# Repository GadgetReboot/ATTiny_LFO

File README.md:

# ATTiny_LFO
<br><br><BR><BR>
Dual low frequency oscillators using ATTiny and MCP4725 DACs

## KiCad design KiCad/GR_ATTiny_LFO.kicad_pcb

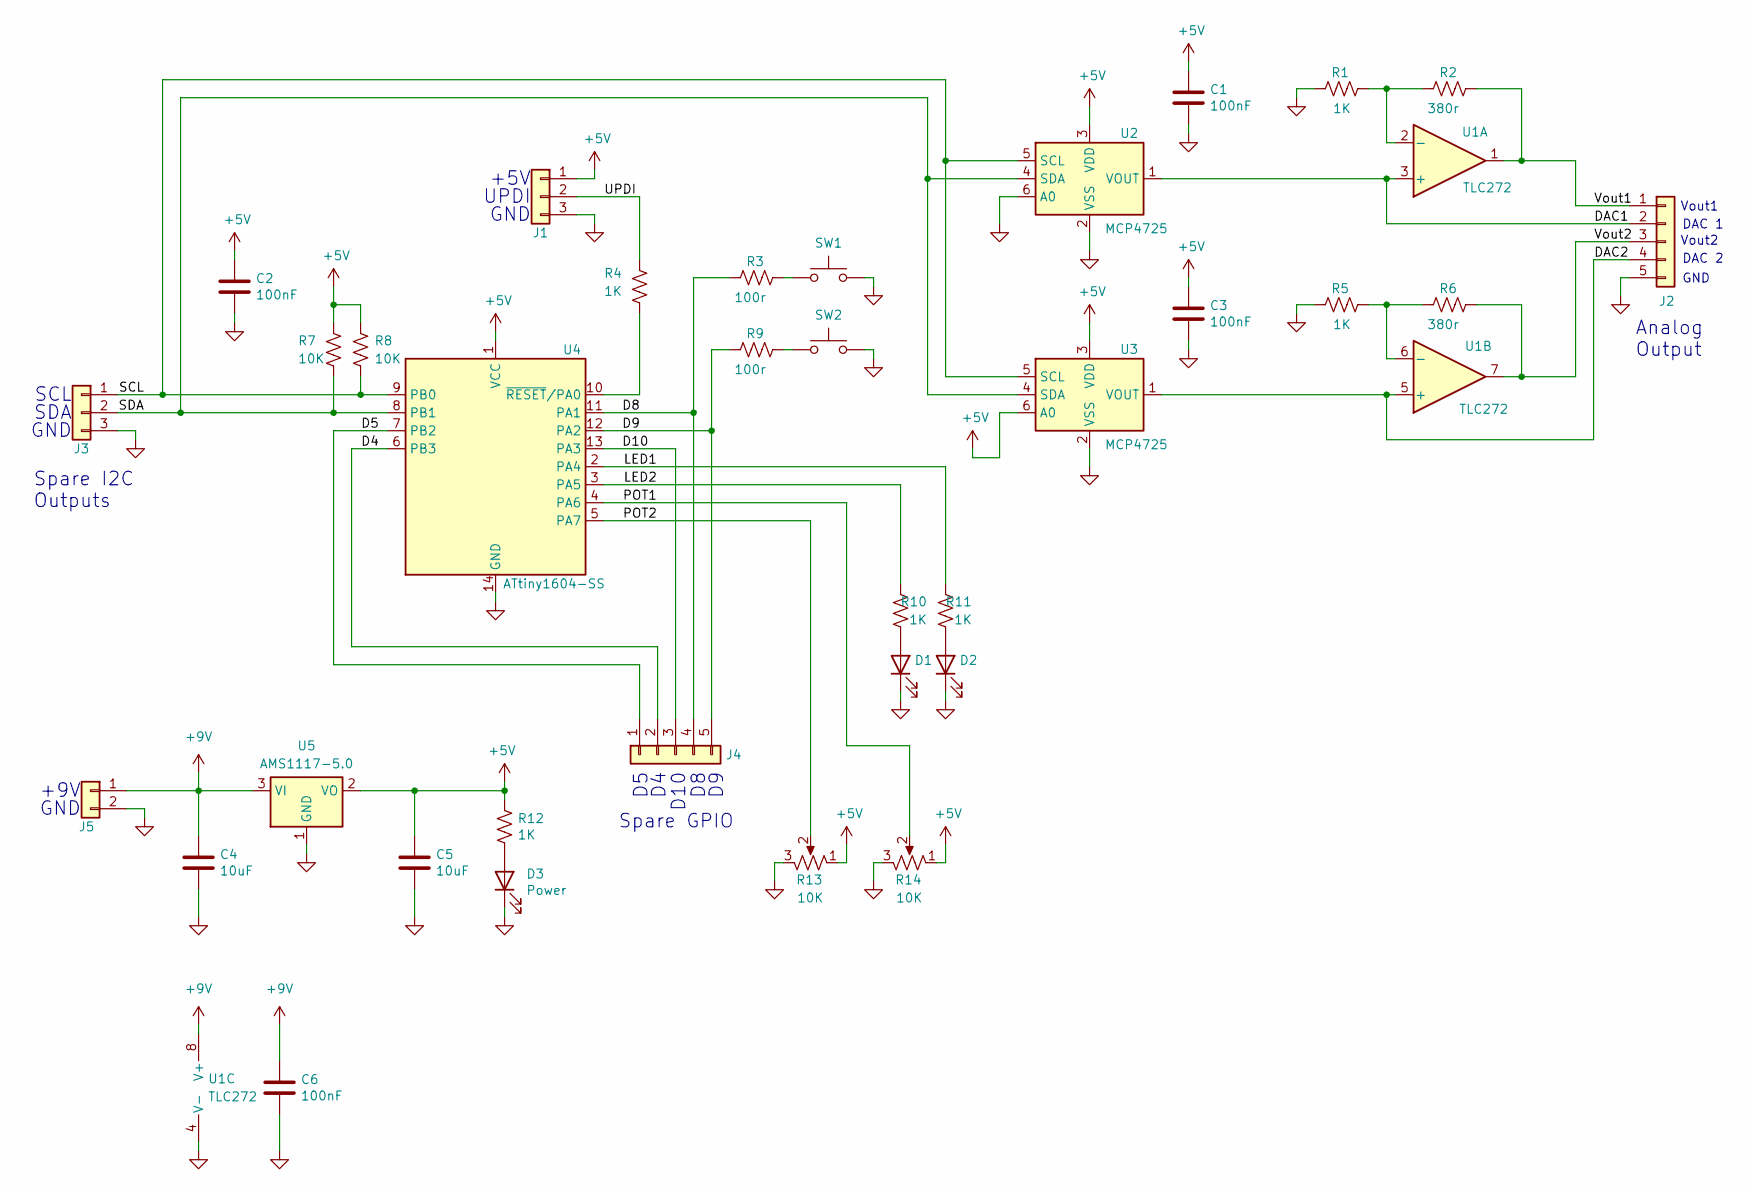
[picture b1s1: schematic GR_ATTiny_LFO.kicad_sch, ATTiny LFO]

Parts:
C1, C3, C6: 100nF; C_0805_2012Metric_Pad1.15x1.40mm_HandSolder
C2: 100nF; C_0805_2012Metric_Pad1.18x1.45mm_HandSolder
C4, C5: 10uF; C_0805_2012Metric_Pad1.15x1.40mm_HandSolder
D1, D2: LED; LED_0805_2012Metric_Pad1.15x1.40mm_HandSolder
D3: Power; LED_0805_2012Metric_Pad1.15x1.40mm_HandSolder
J1, J3: Conn_01x03; PinHeader_1x03_P2.54mm_Vertical
J2, J4: Conn_01x05; PinHeader_1x05_P2.54mm_Vertical
J5: 1x2; PinHeader_1x02_P2.54mm_Vertical
R1, R4, R5, R10, R11, R12: 1K; R_0805_2012Metric_Pad1.15x1.40mm_HandSolder
R2, R6: 380r; R_0805_2012Metric_Pad1.15x1.40mm_HandSolder
R3, R9: 100r; R_0805_2012Metric_Pad1.15x1.40mm_HandSolder
R7, R8: 10K; R_0805_2012Metric_Pad1.15x1.40mm_HandSolder
R13, R14: 10K; Potentiometer_Bourns_PTV09A-1
SW1, SW2: SW_Push; SW_SPST_60x35
U1: TLC272; SOIC-8_3.9x4.9mm_P1.27mm
U2, U3: MCP4725; SOT-23-6
U4: ATtiny1604-SS; SOIC-14_3.9x8.7mm_P1.27mm
U5: AMS1117-5.0; SOT-223-3_TabPin2

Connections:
+5V: C1.1, C2.1, C3.1, C5.1, J1.1, R7.1, R8.1, R12.1, R13.1, R14.1, U2.3 (VDD), U3.3 (VDD), U3.6 (A0), U4.1 (VCC), U5.2 (VO)
+9V: C4.1, C6.1, J5.1, U1.8 (V+), U5.3 (VI)
/D4: J4.2, U4.6 (PB3)
/D5: J4.1, U4.7 (PB2)
/D8: J4.4, R3.1, U4.11 (PA1)
/D9: J4.5, R9.1, U4.12 (PA2)
/D10: J4.3, U4.13 (PA3)
/DAC1: J2.2, U1.3 (+), U2.1 (VOUT)
/DAC2: J2.4, U1.5 (+), U3.1 (VOUT)
/LED1: R11.2, U4.2 (PA4)
/LED2: R10.2, U4.3 (PA5)
/POT1: R14.2, U4.4 (PA6)
/POT2: R13.2, U4.5 (PA7)
/SCL: J3.1, R8.2, U2.5 (SCL), U3.5 (SCL), U4.9 (PB0)
/SDA: J3.2, R7.2, U2.4 (SDA), U3.4 (SDA), U4.8 (PB1)
/UPDI: J1.2, R4.1
/Vout1: J2.1, R2.2, U1.1
/Vout2: J2.3, R6.2, U1.7
GND: C1.2, C2.2, C3.2, C4.2, C5.2, C6.2, D1.1 (K), D2.1 (K), D3.1 (K), J1.3, J2.5, J3.3, J5.2, R1.1, R5.1, R13.3, R14.3, SW1.2, SW2.2, U1.4 (V-), U2.2 (VSS), U2.6 (A0), U3.2 (VSS), U4.14 (GND), U5.1 (GND)
unnamed: D1.2 (A), R10.1
unnamed: D2.2 (A), R11.1
unnamed: D3.2 (A), R12.2
unnamed: R3.2, SW1.1
unnamed: R9.2, SW2.1
unnamed: R1.2, R2.1, U1.2 (-)
unnamed: R5.2, R6.1, U1.6 (-)
unnamed: R4.2, U4.10 (~RESET/PA0)

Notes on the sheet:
UPDI
GND
Spare GPIO
+5V
SDA
+9V
Spare I2C Outputs
DAC 2
D10
Vout2
Vout1
DAC 1
SCL
Analog Output

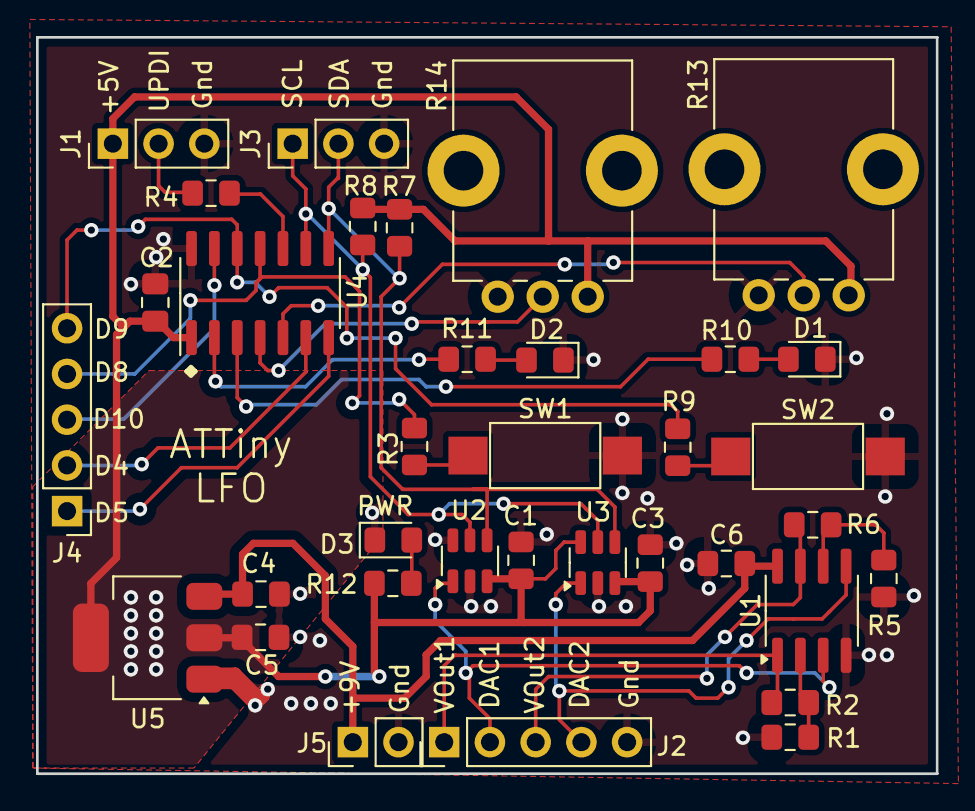
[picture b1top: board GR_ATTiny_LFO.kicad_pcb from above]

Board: 2 copper layers, 50.0 x 40.9 mm, 35 parts (0 on the bottom side), 27 nets.

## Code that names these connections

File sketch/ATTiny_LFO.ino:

/*
     Dual MCP4725 12-bit DACs
     Generating low frequency waveforms
     Uses ATTiny 1604
     Uses Adafruit MCP4725 library
     Uses Bounce2 library https://github.com/thomasfredericks/Bounce2

youtube.com/@GadgetReboot
*/

#include <Wire.h>
#include <Bounce2.h>
#include <Adafruit_MCP4725.h>

// create objects to access the LFO dacs
Adafruit_MCP4725 LFO1;
Adafruit_MCP4725 LFO2;

// button debouncers
Bounce button1 = Bounce();
Bounce button2 = Bounce();

// button and led pins assigned to Arduino digital pin numbers by mapping chip port pins from
// https://github.com/SpenceKonde/megaTinyCore/blob/master/megaavr/extras/ATtiny_x04.md
const byte btn1 = 8;
const byte btn2 = 9;
const byte led1 = 0;
const byte led2 = 1;
const byte pot1 = 2;
const byte pot2 = 3;

// sine waveform data table
const PROGMEM uint16_t sine_data[256] = {
  2048, 2098, 2148, 2198, 2248, 2298, 2348, 2398,
  2447, 2496, 2545, 2594, 2642, 2690, 2737, 2784,
  2831, 2877, 2923, 2968, 3013, 3057, 3100, 3143,
  3185, 3226, 3267, 3307, 3346, 3385, 3423, 3459,
  3495, 3530, 3565, 3598, 3630, 3662, 3692, 3722,
  3750, 3777, 3804, 3829, 3853, 3876, 3898, 3919,
  3939, 3958, 3975, 3992, 4007, 4021, 4034, 4045,
  4056, 4065, 4073, 4080, 4085, 4089, 4093, 4094,
  4095, 4094, 4093, 4089, 4085, 4080, 4073, 4065,
  4056, 4045, 4034, 4021, 4007, 3992, 3975, 3958,
  3939, 3919, 3898, 3876, 3853, 3829, 3804, 3777,
  3750, 3722, 3692, 3662, 3630, 3598, 3565, 3530,
  3495, 3459, 3423, 3385, 3346, 3307, 3267, 3226,
  3185, 3143, 3100, 3057, 3013, 2968, 2923, 2877,
  2831, 2784, 2737, 2690, 2642, 2594, 2545, 2496,
  2447, 2398, 2348, 2298, 2248, 2198, 2148, 2098,
  2048, 1997, 1947, 1897, 1847, 1797, 1747, 1697,
  1648, 1599, 1550, 1501, 1453, 1405, 1358, 1311,
  1264, 1218, 1172, 1127, 1082, 1038, 995, 952,
  910, 869, 828, 788, 749, 710, 672, 636,
  600, 565, 530, 497, 465, 433, 403, 373,
  345, 318, 291, 266, 242, 219, 197, 176,
  156, 137, 120, 103, 88, 74, 61, 50,
  39, 30, 22, 15, 10, 6, 2, 1,
  0, 1, 2, 6, 10, 15, 22, 30,
  39, 50, 61, 74, 88, 103, 120, 137,
  156, 176, 197, 219, 242, 266, 291, 318,
  345, 373, 403, 433, 465, 497, 530, 565,
  600, 636, 672, 710, 749, 788, 828, 869,
  910, 952, 995, 1038, 1082, 1127, 1172, 1218,
  1264, 1311, 1358, 1405, 1453, 1501, 1550, 1599,
  1648, 1697, 1747, 1797, 1847, 1897, 1947, 1997
};

// triangle waveform data table
// generated using https://www.daycounter.com/Calculators/Triangle-Wave-Generator-Calculator.phtml
const PROGMEM int16_t triangle_data[256] = {
  32, 64, 96, 128, 160, 192, 224, 256,
  288, 320, 352, 384, 416, 448, 480, 512,
  544, 576, 608, 640, 672, 704, 736, 768,
  800, 832, 864, 896, 928, 960, 992, 1024,
  1056, 1088, 1120, 1152, 1184, 1216, 1248, 1280,
  1312, 1344, 1376, 1408, 1440, 1472, 1504, 1536,
  1568, 1600, 1632, 1664, 1696, 1728, 1760, 1792,
  1824, 1856, 1888, 1920, 1952, 1984, 2016, 2048,
  2079, 2111, 2143, 2175, 2207, 2239, 2271, 2303,
  2335, 2367, 2399, 2431, 2463, 2495, 2527, 2559,
  2591, 2623, 2655, 2687, 2719, 2751, 2783, 2815,
  2847, 2879, 2911, 2943, 2975, 3007, 3039, 3071,
  3103, 3135, 3167, 3199, 3231, 3263, 3295, 3327,
  3359, 3391, 3423, 3455, 3487, 3519, 3551, 3583,
  3615, 3647, 3679, 3711, 3743, 3775, 3807, 3839,
  3871, 3903, 3935, 3967, 3999, 4031, 4063, 4095,
  4063, 4031, 3999, 3967, 3935, 3903, 3871, 3839,
  3807, 3775, 3743, 3711, 3679, 3647, 3615, 3583,
  3551, 3519, 3487, 3455, 3423, 3391, 3359, 3327,
  3295, 3263, 3231, 3199, 3167, 3135, 3103, 3071,
  3039, 3007, 2975, 2943, 2911, 2879, 2847, 2815,
  2783, 2751, 2719, 2687, 2655, 2623, 2591, 2559,
  2527, 2495, 2463, 2431, 2399, 2367, 2335, 2303,
  2271, 2239, 2207, 2175, 2143, 2111, 2079, 2048,
  2016, 1984, 1952, 1920, 1888, 1856, 1824, 1792,
  1760, 1728, 1696, 1664, 1632, 1600, 1568, 1536,
  1504, 1472, 1440, 1408, 1376, 1344, 1312, 1280,
  1248, 1216, 1184, 1152, 1120, 1088, 1056, 1024,
  992, 960, 928, 896, 864, 832, 800, 768,
  736, 704, 672, 640, 608, 576, 544, 512,
  480, 448, 416, 384, 352, 320, 288, 256,
  224, 192, 160, 128, 96, 64, 32, 0
};


void setup(void) {

  // For MCP4725A0 the address is 0x60 or 0x61
  LFO1.begin(0x60);
  LFO2.begin(0x61);

  pinMode(btn1, INPUT_PULLUP);  // button input pin
  pinMode(btn2, INPUT_PULLUP);  // button input pin
  pinMode(led1, OUTPUT);        // LED1
  pinMode(led2, OUTPUT);        // LED2

  button1.attach(btn1);  // button debouncer
  button1.interval(30);  // interval in ms
  button2.attach(btn2);  // button debouncer
  button2.interval(30);  // interval in ms

  // test blink LEDs on power up
  digitalWrite(led1, HIGH);
  delay(500);
  digitalWrite(led1, LOW);

  digitalWrite(led2, HIGH);
  delay(500);
  digitalWrite(led2, LOW);
}

void loop(void) {

  for (int i = 0; i < 256; i++) {
    // write next data sample to each DAC to generate waveforms
    LFO1.setVoltage(pgm_read_word(&(sine_data[i])), false);
    LFO2.setVoltage(pgm_read_word(&(triangle_data[i])), false);
    /*
    // process button presses
    button1.update();
    if (button1.fell()) {  // if button was pressed
      digitalWrite(led1, HIGH);
      delay(10);
      digitalWrite(led1, LOW);
    }

    button2.update();
    if (button2.fell()) {  // if button was pressed
      digitalWrite(led2, HIGH);
      delay(10);
      digitalWrite(led2, LOW);
    }
*/

    // control the rate of sample writing on the DACs to set the waveform frequency
    int delayTime = analogRead(pot1);
    delayTime = map(delayTime, 0, 1023, 20000, 0);  // map pot voltage on ADC to a uS delay so that ccw to cw is a low to high frequency waveform
    delayMicroseconds(delayTime);

    // make LED brightness follow the waveform frequency by using pwm brightness control
    if (i < 128)
      analogWrite(led1, map(i, 0, 256, 0, 64));  // ramp brightness up for first half of wave cycle
    else
      analogWrite(led1, map(i, 0, 256, 64, 0));  // ramp brightness down for second half of wave cycle
  }
}
